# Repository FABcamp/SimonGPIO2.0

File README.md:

SimonGPIO2.0
============

SimonGPIO files for UCI fabcamp 2.0

includes:
 - Eagle BRD files, requires the [Sparkfun Eagle library][] and [Adafruit Eagle library][]
[Sparkfun Eagle library]: <https://github.com/sparkfun/SparkFun-Eagle-Libraries>
[Adafruit Eagle library]: <https://github.com/adafruit/Adafruit-Eagle-Library>
 - Fritzing PCB layout with custom part files for [Square buttons sold by Adafruit][]
[Square buttons sold by Adafruit]: <http://www.adafruit.com/products/1010>
 - solidworks and STL files for the Case and a test model of the finished PCB
 - scratch files and [instructions][] for running the project
[instructions]: https://github.com/FabCamp/SimonGPIO2.0/blob/master/Documentation/Scratch%20Instructions.md
 - [Bill of Materials][] for the project
[Bill of Materials]: https://github.com/FabCamp/SimonGPIO2.0/blob/master/Documentation/Bill%20Of%20Materials.md

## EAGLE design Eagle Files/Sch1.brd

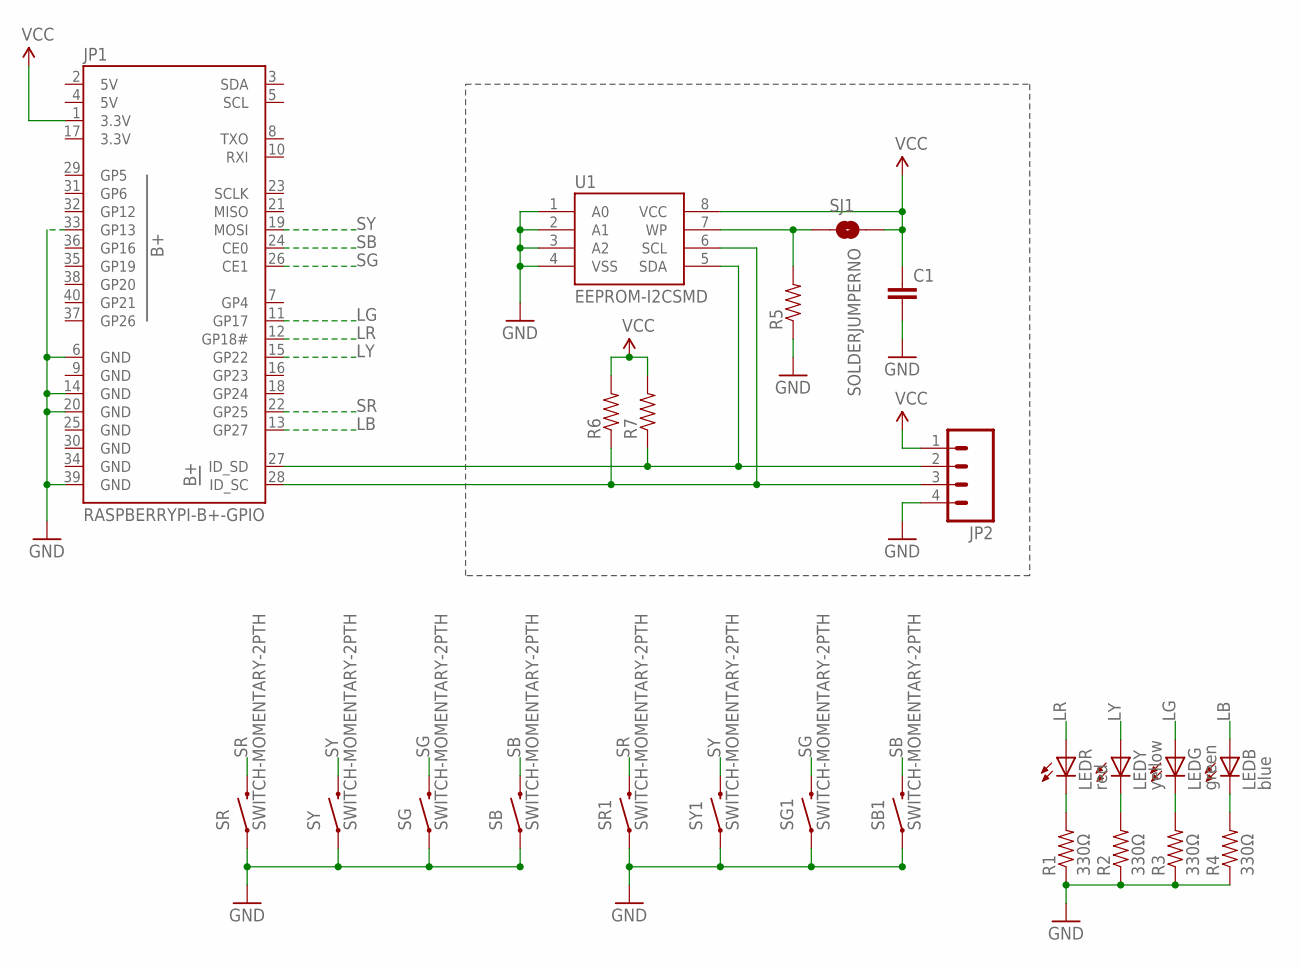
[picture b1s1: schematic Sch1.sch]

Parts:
C1: CAP0805; 0805
JP1: RASPBERRYPI-B+-GPIO; 2X20-SHROUDED
JP2: M04PTH; 1X04
LEDB: blue; LED5MM
LEDG: green; LED5MM
LEDR: red; LED5MM
LEDY: yellow; LED5MM
R1, R2, R3, R4: 330Ω; AXIAL-0.4
R5, R6, R7: RESISTOR0805-RES; 0805
SB, SB1: SWITCH-MOMENTARY-2PTH; TACTILE-PTH
SG, SG1: SWITCH-MOMENTARY-2PTH; TACTILE-PTH
SJ1: SOLDERJUMPERNO; SJ_2S-NO
SR, SR1: SWITCH-MOMENTARY-2PTH; TACTILE-PTH
SY, SY1: SWITCH-MOMENTARY-2PTH; TACTILE-PTH
U1: EEPROM-I2CSMD; SO08

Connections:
3.3V: JP1.17 (3.3V)
5V: JP1.2 (5V), JP1.4 (5V)
GND: C1.2, JP1.6 (GND), JP1.9 (GND), JP1.14 (GND), JP1.20 (GND), JP1.25 (GND), JP1.30 (GND), JP1.33 (GP13), JP1.34 (GND), JP1.39 (GND), JP2.4, R1.P$1 (1), R2.P$1 (1), R3.P$1 (1), R4.P$1 (1), R5.1, SB.1, SB1.1, SG.1, SG1.1, SR.1, SR1.1, SY.1, SY1.1, U1.1 (A0), U1.2 (A1), U1.3 (A2), U1.4 (VSS)
LB: JP1.13 (GP27), LEDB.A
LG: JP1.11 (GP17), LEDG.A
LR: JP1.12 (GP18#), LEDR.A
LY: JP1.15 (GP22), LEDY.A
unnamed: LEDR.K (C), R1.P$2 (2)
unnamed: LEDY.K (C), R2.P$2 (2)
unnamed: LEDG.K (C), R3.P$2 (2)
unnamed: LEDB.K (C), R4.P$2 (2)
unnamed: JP1.27 (ID_SD), JP2.2, R7.1, U1.5 (SDA)
unnamed: JP1.28 (ID_SC), JP2.3, R6.1, U1.6 (SCL)
unnamed: R5.2, SJ1.1, U1.7 (WP)
SB: JP1.24 (CE0), SB.3 (2), SB1.3 (2)
SG: JP1.26 (CE1), SG.3 (2), SG1.3 (2)
SR: JP1.22 (GP25), SR.3 (2), SR1.3 (2)
SY: JP1.19 (MOSI), SY.3 (2), SY1.3 (2)
VCC: C1.1, JP1.1 (3.3V), JP2.1, R6.2, R7.2, SJ1.2, U1.8 (VCC)

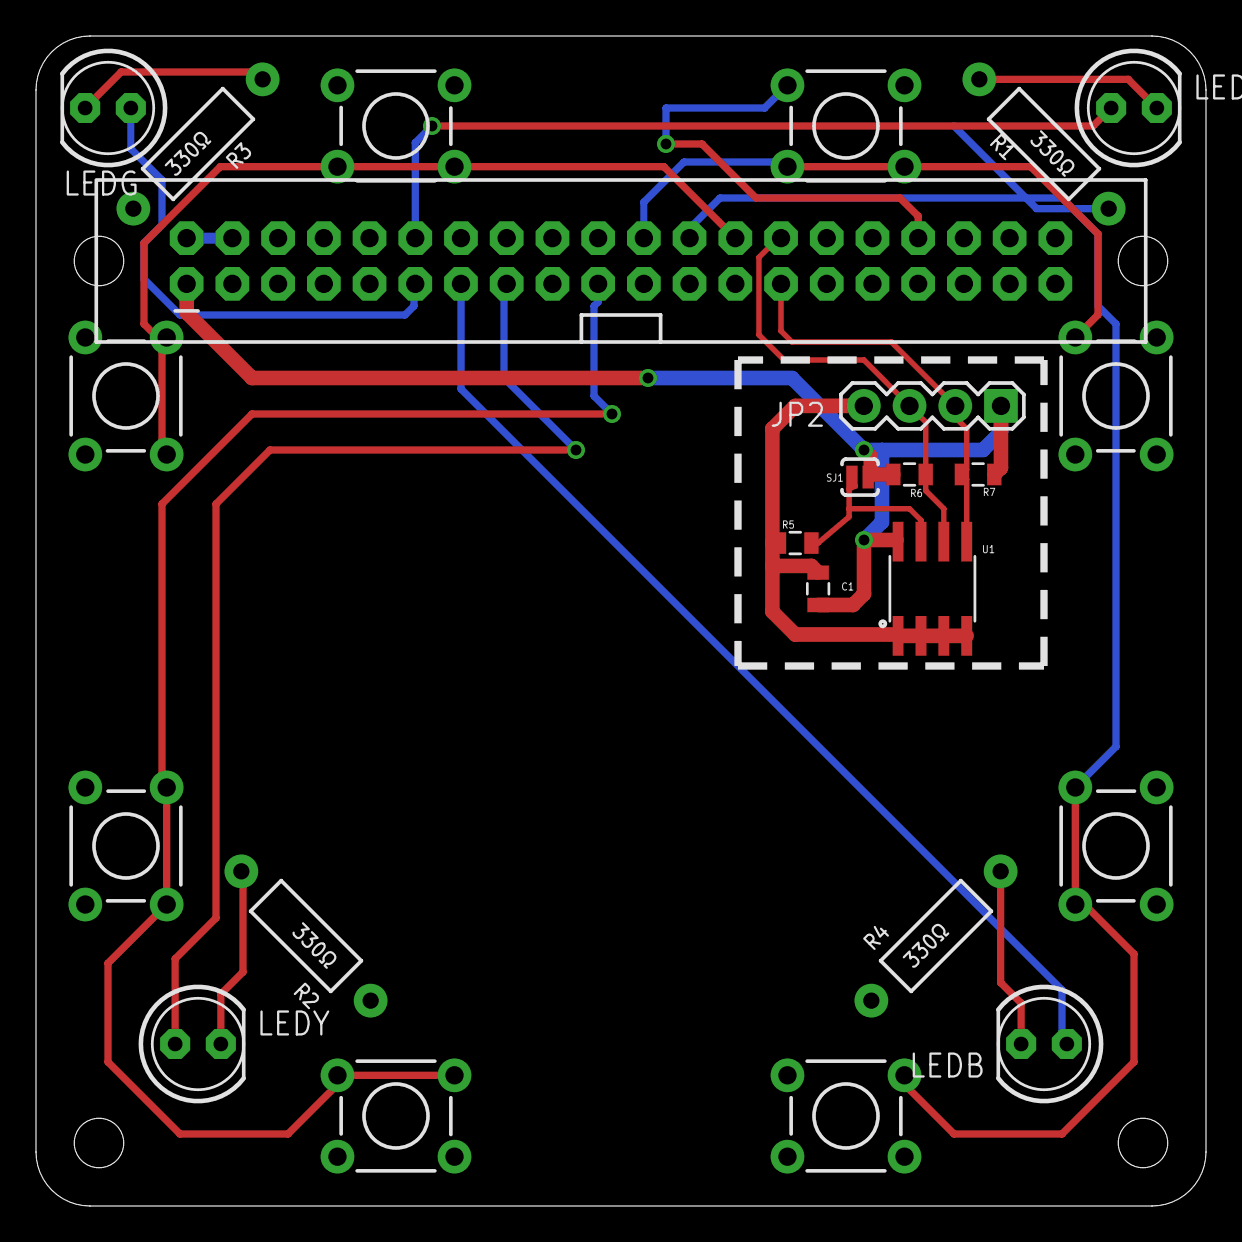
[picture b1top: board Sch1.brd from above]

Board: 2 copper layers, 65.0 x 65.0 mm, 24 parts (0 on the bottom side), 18 nets.

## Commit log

2014-07-03 Add Solidworks and STL files for case
2014-07-03 Create Scratch Instructions
2014-07-03 Add image for instructions
2014-07-07 Add Bill of Materials
2014-07-07 oops
2014-07-07 Fix Image Links
2014-07-07 Hello yes this is derp
2014-07-07 Update Readme with links to some project files
2014-07-11 Move Documentation to Documentation Folder
2014-07-11 Fix broken links in Readme.md
2014-07-11 add .DS_store to .gitignore
2014-07-11 Add more steps to Fritzing files with Images
2014-07-11 Add transparency to Breadboard Images
2014-07-11 Fix Transparency on Breadboard GND-Wires.png
2014-07-11 Clean up Breadboard Images
    • add 200px border around images
    • remove stray white pixels
2014-07-11 Change from 3 parts to 2 in Scratch Instruction
2014-07-15 how does I maths????
2015-06-24 Move wiki files into repo proper
2015-06-24 Update Bill Of Materials.md
    Complete overhaul for 2015
2015-06-25 Update PCB design for this year, minor tweaks
2015-06-25 Regenerate GERBER files
2015-06-25 Adjust markings for Ribbon Cable connector
2015-06-25 Update Simon-completed to new form of code
2015-06-25 update scratch.gif to reflect recent update to code
2015-06-25 add eagle temporary files to gitignore
2015-06-25 ignore .b#* files
2015-06-25 Add version number
2015-06-25 Formatting
2015-06-25 Add downgrade cable to BOM
    Added Downgrade Cable to the BOM to work with the 40 pin Pi 2 GPIO header
2015-06-25 Add totals
2015-06-25 bold totals
2015-06-25 Add our estimated value from Bay Area Circuits
2015-06-25 Add disclaimer on soldering materials
2015-06-25 add break in connector outline for via
2015-06-26 Rename Building-the-Breadboard.md to Building the Breadboard.md
2015-06-26 move position of Downgrade cable in PCB list
    • Moved the position of the Downgrade cable in the PCB materials list to better match the previous list
2015-06-26 italicize materials that can be reused
2015-06-26 Correct subheading for PCBs section
    • change subsection of the PCBs section to match that of others in the document
2015-06-26 Disclaimer on extra components
    add a disclaimer on getting extra components
2015-06-26 Round corners of PCB
    • Round corners of PCB
    • move mounting holes to all four corners
2015-06-26 Add image illustrating breadboard connections
2015-06-26 Change mounting hole drill sizes
    • change mounting holes from 2.8mm to 3mm
    • updated version number
2015-06-26 Change width of back silkscreen fill
2015-06-26 update Gerber Files
2015-06-26 Add front outline and socket fix
    + Add outline to frong
    • fix box header outline
2015-06-26 update version
2015-06-26 remove temporary file
2015-06-26 Export new Gerber files
2015-06-27 Add CAM job
2015-06-27 Update and reorganize solid works files
2015-06-27 more tweaks to Solidworks files
2015-06-27 add Screw and Spacer files
    (assembly should now work)
2015-06-27 add adobe illustrator drawings
2015-06-27 add PDFs of drawings
2015-06-27 move non-solidworks drawings
2015-06-27 remove free version disclaimer from assembly drawing
2015-06-27 Update eagle project file
    This software has some really weird config files
2015-06-27 add breadboard paths frizzing file
2015-06-28 add PCB illustrations for front and back
2015-06-29 add images for cloning
2015-06-29 add compound image
2015-06-29 Add hardware to Bill of Materials
2015-06-30 add model column for later
2015-06-30 Reorganize part files
2015-06-30 More updates
2015-06-30 Add final assembly
2015-06-30 iunno
2015-06-30 ¯\_(ツ)_/¯
2015-07-01 more updating
2015-07-01 add save for appearance?
2015-07-07 update case
2015-07-07 lower tolerance around buttons slightly
2015-07-07 raise height of LEDs in case for flexibility
2015-07-07 update case file to match recent changes
2015-07-07 reorient case and assembly models for better viewing
2015-07-07 final changes to assembly
2015-07-07 remove temporary files
    i thought i chose to ignore these…
2015-07-07 help there are more
2015-07-07 ignore solidworks temp files
2015-07-07 add version number to part model
2015-07-07 Revert 1682bb6..73902a2
    This rolls back to commit 1682bb6f1faba2033edf4862bf592824650a5027.
2015-07-07 add version number to case file
2015-07-07 Revert "add version number to case file"
    This reverts commit f0a68ef5de1f65eca20f909cd8c7334c396250a6.
2015-07-10 fix .gitignore for Solidworks temp files
2015-07-10 Configure different sizes and colors of LEDs
2015-07-10 add DFX file
2015-07-20 disclaimer for teachers and proper title
2015-07-27 uhhhhh
2015-11-27 Update Files
2016-06-13 Update BOM for raspberry pis for 2016
2016-06-13 Consolidate BOM since we are no longer running APPcamp
2016-06-13 minor fixes
2016-06-15 Fix monoprice link
2016-07-12 fix bill of materials
2016-07-14 update case file
2016-07-15 add simon.py
2016-07-15 Move completed simon project to new file
    - Move completed Simon project to a new file
    - Truncate Simon.py to become the starter file

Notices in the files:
parts and their libraries:
SparkFun-Passives: Licensing: Creative Commons ShareAlike 4.0 International - https://creativecommons.org/licenses/by-sa/4.0
